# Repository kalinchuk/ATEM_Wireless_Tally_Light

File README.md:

# ATEM Wireless Tally Light

Wireless tally light system for ATEM switchers.

## Setup and Configuration

Note: We're assuming that you have a transmitter board with the Arduino Ethernet and also a receiver board with a JeeNode. If not, visit [http://kvitko.com/tally](http://kvitko.com/tally).

1.  Copy the dependent libraries from the project's libraries directory to your systems Arduino libraries directory. You may need to overwrite some of the libraries.
1.  Upload `ATEM_Tally_Receiver.ino` to your receiver node.
1.  Upload `ATEM_Tally_Transmitter.ino` to your transmitter.
1.  Connect the transmitter to the same network as the ATEM switcher and power it on (it may take a minute to connect to ATEM).
1.  Set the node # on your receiver using the DIP pins. It will blink the node # on power-on.

Once connected, the receiver will light up RED if on PROGRAM and GREEN if on PREVIEW.

## Transmitter

A transmitter transmits ATEM PROGRAM and PREVIEW camera numbers using an RF12 radio.

### Default Settings

	IP address		: 192.168.1.234
	Mac address 	: DE:AD:BE:EF:FE:ED
	Switcher IP		: 192.168.1.240
	Switcher PORT	: 49910

The settings can be modified using the web interface [http://192.168.1.234/](http://192.168.1.234/) or reset using the RESET button on the transmitter.

### LED States

The following are transmitter LED states:

	RED 		: Not connected to network (or ATEM switcher)
	BLUE 		: Connected to ATEM switcher
	RED BLINK	: Radio signal sent

## Receiver

A receiver receives radio signals from the transmitter and triggers either the PROGRAM LED or the PREVIEW LED according to the transmitter and ATEM.

### LED States

The following are receiver LED states:

	POWER-ON BLUE BLINK	: Blinks node # or rapidly for test mode
	CONSTANT BLUE BLINK	: In test mode (receiving radio signal)
	RED					: Node # is on PROGRAM
	GREEN				: Node # is on PREVIEW

### Test Mode

Setting the receiver's node # to 0 (all DIP pins off) will switch it to _test mode_. When in _test mode_ the receiver will blink BLUE every 1 second if it's receiving a radio signal. On power-on in _test mode_ the LED will blink BLUE rapidly for a second or so.

### Node DIP Pins

The node DIP pins are binary-based. For example, when the DIP pins are `0110`, the node # is `5`.

Note: The receiver needs to be restarted whenever the node # is changed.

## Library Modifications

The RF12 library was slightly modified to allow the Arduino Ethernet to support both the Ethernet and the RF12 radio. Since Ethernet and the radio both use the same `SS_BIT`, they will conflict with each other. Leave Ethernet as it is and modify the RF12 library only. 

Note: There is a new class called `RF12Mod` which is a copy of `RF12` with slight modifications.

## Credits

Based on the [Arduino ATEM Library](https://github.com/kasperskaarhoj/Arduino-Library-for-ATEM-Switchers)

## Contributing

We welcome any contributions and bug fixes. Feel free to send pull requests.

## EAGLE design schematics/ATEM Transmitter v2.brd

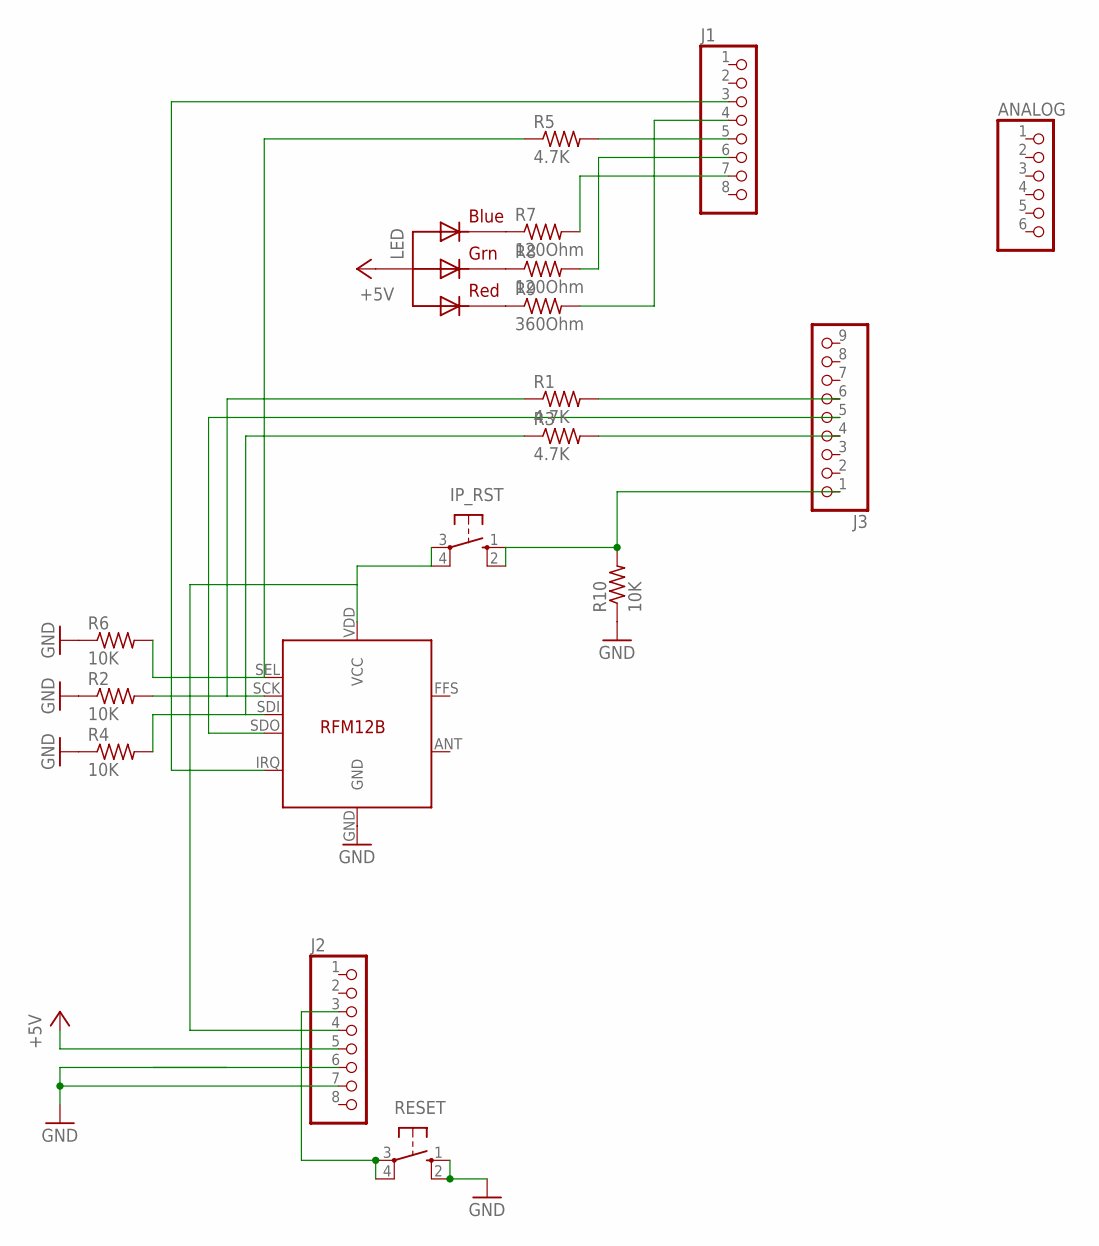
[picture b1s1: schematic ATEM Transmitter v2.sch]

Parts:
ANALOG: PINHD-1X6; 1X06
IP_RST: 10-XX; B3F-10XX
J1, J2: PINHD-1X8TH; 1X08-TH
J3: PINHD-1X9; 1X09
LED: RGBLED_CA-5MM; LED5MMRGB
R1, R3, R5: 4.7K; R0805
R2, R4, R6, R10: 10K; R0805
R7, R8: 120Ohm; R0805
R9: 360Ohm; R0805
RESET: 10-XX; B3F-10XX
U$2: RFM12B; LH-LIBRARY_RFM12B

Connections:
+5V: J2.5, LED.2 (VCC)
GND: J2.7, R2.1, R4.1, R6.1, R10.1, RESET.1 (S), RESET.2 (S1), U$2.GND
unnamed: IP_RST.3, IP_RST.4 (P1), J2.4, U$2.VDD (VCC)
unnamed: J3.6, R1.2
unnamed: R1.1, R2.2, U$2.SCK
unnamed: J1.3, U$2.IRQ
unnamed: R3.1, R4.2, U$2.SDI
unnamed: J3.4, R3.2
unnamed: J3.5, U$2.SDO
unnamed: R5.1, R6.2, U$2.SEL
unnamed: J1.5, R5.2
unnamed: LED.4 (BLUE), R7.1
unnamed: LED.3 (GREEN), R8.1
unnamed: LED.1 (RED), R9.1
unnamed: J1.4, R9.2
unnamed: IP_RST.1 (S), IP_RST.2 (S1), J3.1, R10.2
unnamed: J1.7, R7.2
unnamed: J1.6, R8.2
RESET: J2.3, RESET.3, RESET.4 (P1)

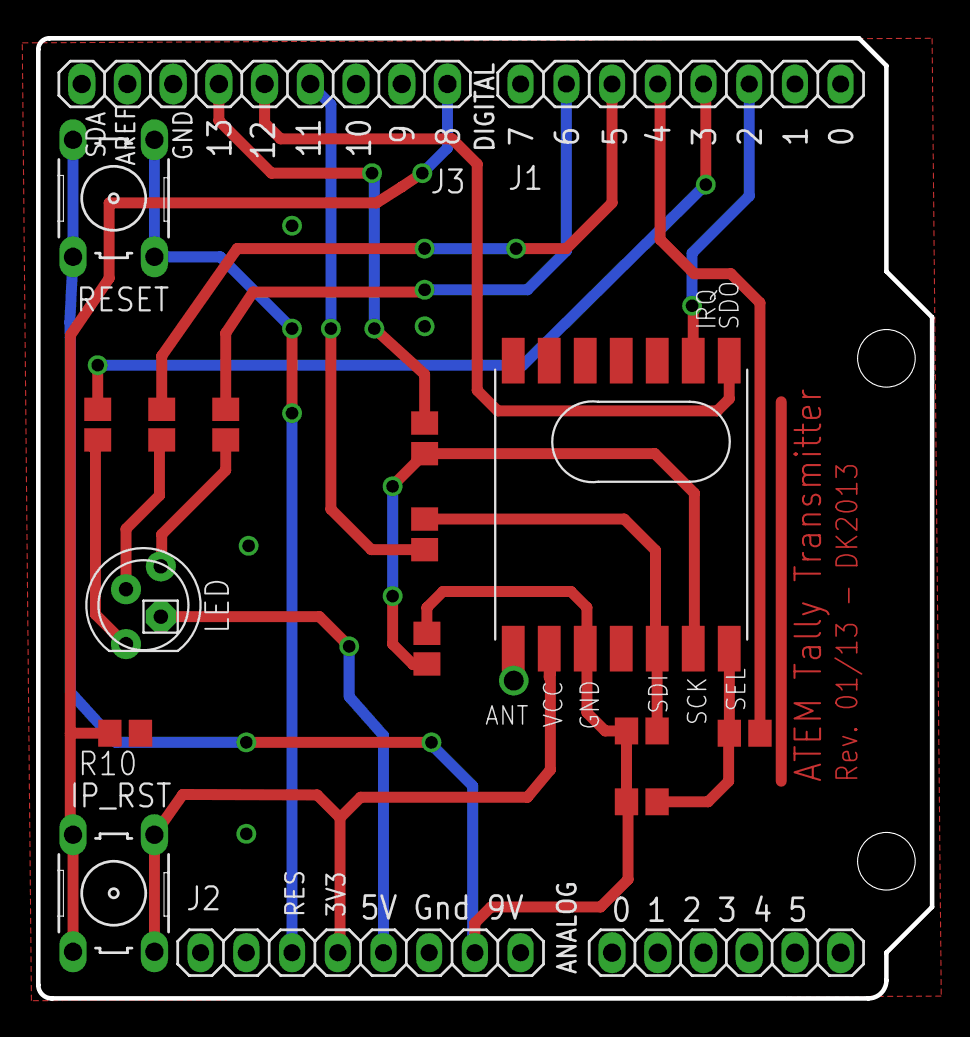
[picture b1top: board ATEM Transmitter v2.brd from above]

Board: 2 copper layers, 49.7 x 53.3 mm, 18 parts (0 on the bottom side), 19 nets.

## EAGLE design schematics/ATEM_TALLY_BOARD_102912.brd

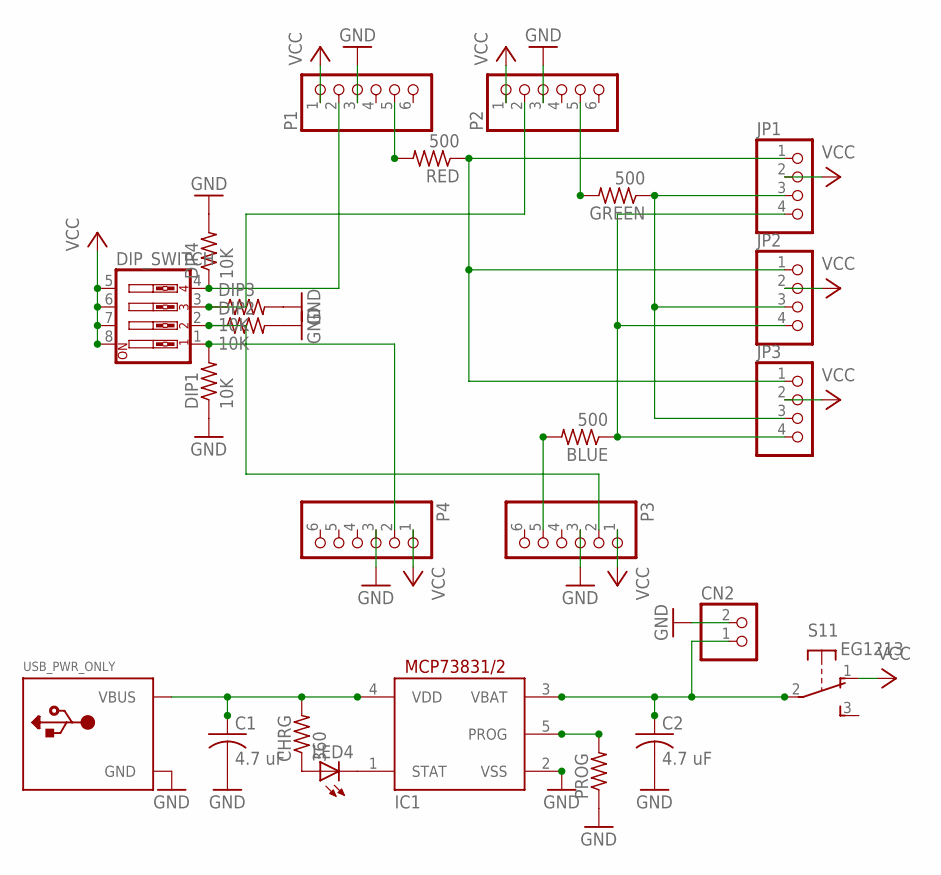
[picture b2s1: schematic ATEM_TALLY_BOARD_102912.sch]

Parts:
BLUE: 500; R0805
C1, C2: 4.7 uF; C0805K
CHRG: 360; R0805
CN2: JST_2PIN-SMT-RA; JST-PH-2-SMT-RA
DIP1, DIP2, DIP3, DIP4: 10K; R0805
DIP_SWITCH: SW_DIP-4; EDG-04
GREEN: 500; R0805
IC1: MCP73831/OT; SOT23-5L
JP1, JP2, JP3: PINHD-1X4; 1X04
LED4: LED3MM
P1, P2, P3, P4: PINHD-1X6CB; 1X06-CLEANBIG
PROG: R-US_R0805; R0805
RED: 500; R0805
S1: EG1213
USB_PWR_ONLY: USB-PWR-NOSILK; USB-MINIB-THM-MOLEX-PWRONLY-NOSILK

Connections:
BLUE: BLUE.1, JP1.4, JP2.4, JP3.4
GND: C1.2, C2.2, CN2.2 (1), DIP1.1, DIP2.2, DIP3.2, DIP4.2, IC1.2 (VSS), P1.3, P2.3, P3.3, P4.3, PROG.1, USB_PWR_ONLY.GND
GREEN: GREEN.1, JP1.3, JP2.3, JP3.3
unnamed: P1.5, RED.2
unnamed: GREEN.2, P2.5
unnamed: BLUE.2, P3.5
unnamed: C1.1, CHRG.2, IC1.4 (VDD), USB_PWR_ONLY.VBUS
unnamed: DIP4.1, DIP_SWITCH.4, P1.2
unnamed: DIP3.1, DIP_SWITCH.3, P2.2
unnamed: DIP2.1, DIP_SWITCH.2, P3.2
unnamed: DIP1.2, DIP_SWITCH.1, P4.2
unnamed: IC1.1 (STAT), LED4.K (C)
unnamed: CHRG.1, LED4.A
unnamed: IC1.5 (PROG), PROG.2
unnamed: C2.1, CN2.1 (2), IC1.3 (VBAT), S1.2
RED: JP1.1, JP2.1, JP3.1, RED.1
VCC: DIP_SWITCH.5, DIP_SWITCH.6, DIP_SWITCH.7, DIP_SWITCH.8, JP1.2, JP2.2, JP3.2, P1.1, P2.1, P3.1, P4.1, S1.1 (O)

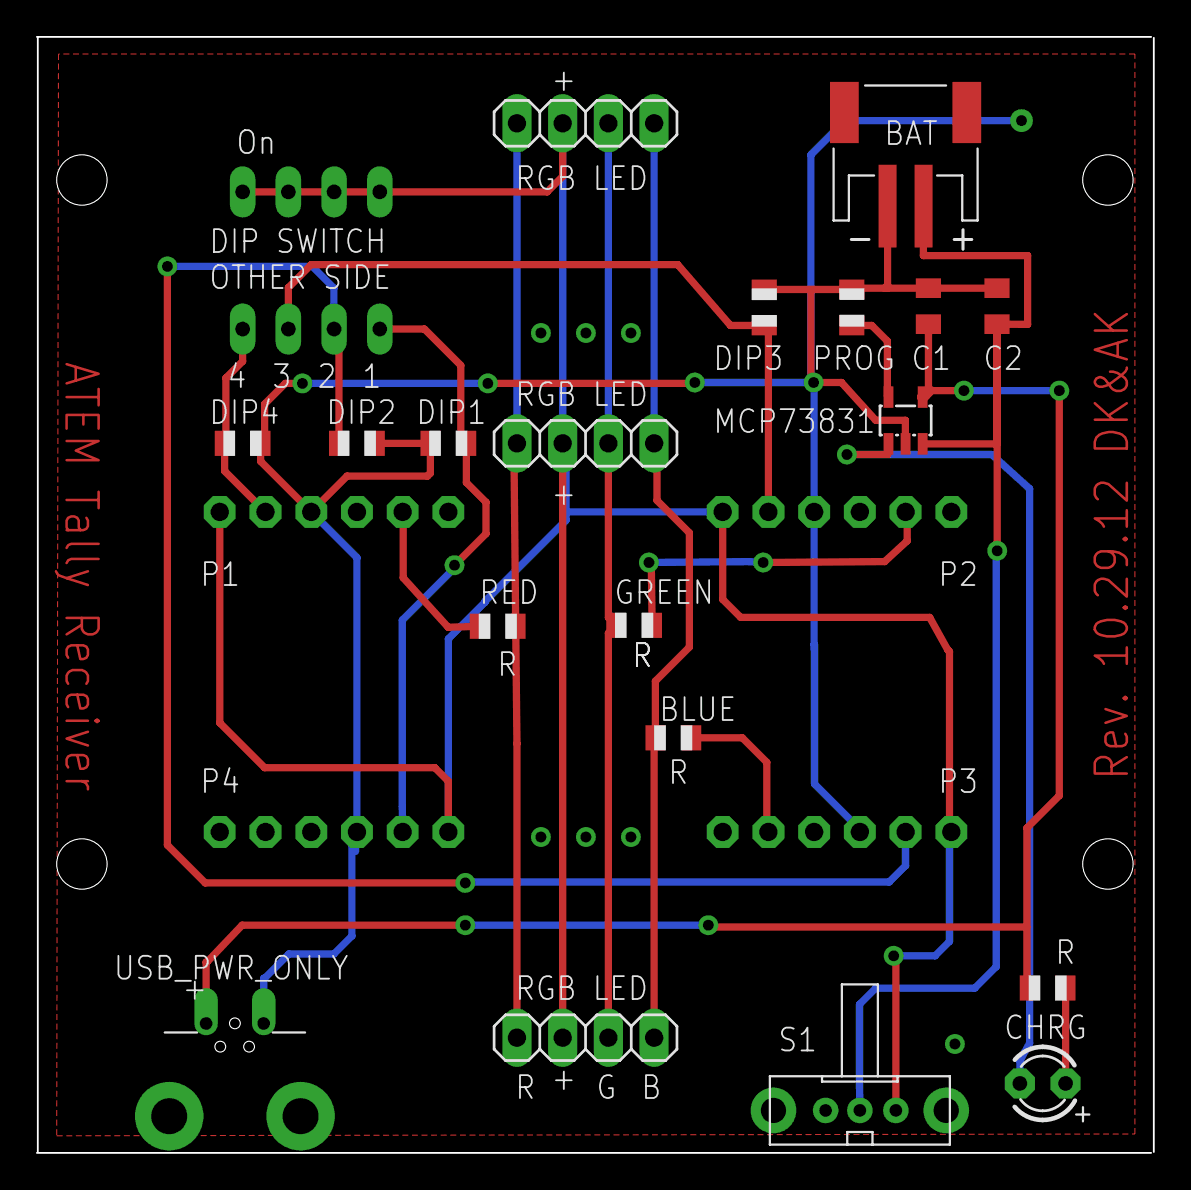
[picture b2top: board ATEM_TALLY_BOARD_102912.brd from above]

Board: 2 copper layers, 62.0 x 62.0 mm, 24 parts (1 on the bottom side), 17 nets.

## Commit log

2013-02-22 Added receiver code, transmitter code, libraries and other dependent code.
2013-02-22 Removed extra file
2013-02-22 Modified the README with more information.
2013-02-22 Fixed some formatting issues.
2013-02-22 Added a link to the transmitter's web interface.
2013-03-06 Added a link to the tally page.
2013-04-30 Create test
2013-04-30 test
2013-05-14 Schematic and board files added
2014-03-08 Upgrade the ATEM library to the 2/23/2014 version - supports the new ATEM firmware.
2014-03-10 Add MIT license.
2016-01-19 Compile on Arduino IDE 1.6.7. Fix bugs including bug where two programs should be on during transition. Upgrade to ATEMstd.
2020-07-13 Update ATEM_Tally_Receiver.ino
    - Corrected use of analogWrite() to digitalWrite()
    - Minor indentation fixes
